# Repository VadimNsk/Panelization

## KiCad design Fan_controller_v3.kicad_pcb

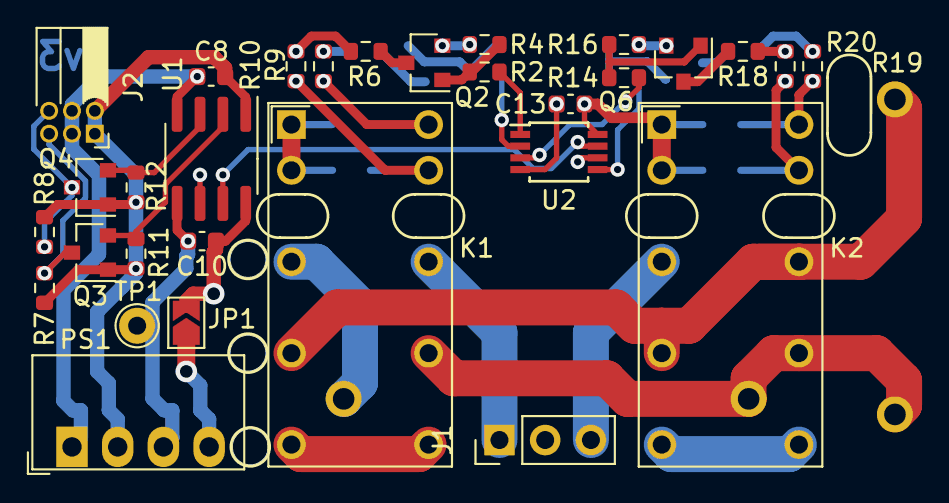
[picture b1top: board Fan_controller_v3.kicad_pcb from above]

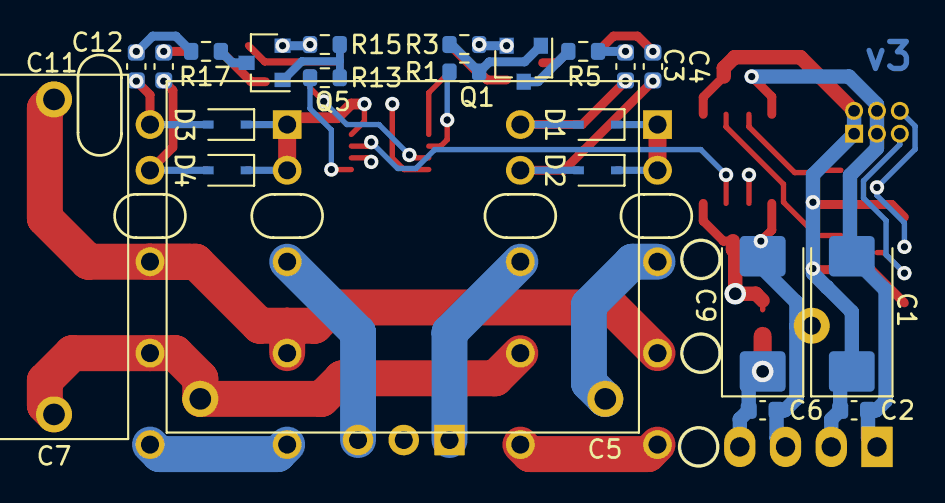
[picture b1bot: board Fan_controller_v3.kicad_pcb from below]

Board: 4 copper layers, 52 parts (22 on the bottom side), 38 nets.

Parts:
C1: 10uF; CP_EIA-7343-43_Kemet-X_Pad2.25x2.55mm_HandSolder
C2, C6, C8, C10, C13: 100nF; C_0603_1608Metric
C3, C4, C11, C12: 10uF; C_0603_1608Metric
C5: 0.47uF; C_K73-17_W26.0mm_H15.0mm_T9.0mm_P22.5mm_d0.8mm_Horiz2
C7: 0.22uF; C_K73-17_W20.0mm_H14.5mm_T8.0mm_P17.5mm_d0.8mm
C9: 100uF; CP_EIA-7343-43_Kemet-X_Pad2.25x2.55mm_HandSolder
D1, D2, D3, D4: 1N4148WS; D_SOD-323
J1: Load2; PinHeader_1x03_P2.54mm
J2: Dig_mod_iface; PinSocket_2x03_P1.27mm_Horizontal
JP1: 5P_en; SolderJumper-2_P1.3mm_Open_TrianglePad1.0x1.5mm
K1, K2: HFD2_005-S-L2-D_Split; HFD2-005-S-L2-D
PS1: B0505S
Q1, Q2, Q5, Q6: 2N5551S; SOT-23
Q3, Q4: BSS138; SOT-23
R1, R2, R13, R14: 1k; R_0603_1608Metric
R3, R4, R15, R16: 20k; R_0603_1608Metric
R5, R6, R17, R18: 47; R_0603_1608Metric
R7, R8: 10G; R_0603_1608Metric
R9, R10, R19, R20: 820; R_0603_1608Metric
R11, R12: 10k; R_0603_1608Metric
TP1: GND; TestPoint_THTPad_D2.0mm_Drill1.0mm
U1: ADuM1251ARZ; SOIC-8_3.9x4.9mm_P1.27mm
U2: PCA9536DP; TSSOP-8_3x3mm_P0.65mm

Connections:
+5P: C1.1, C2.2, C8.2, J2.1, J2.2, PS1.2, Q3.1, Q4.1, R7.2, R8.2, R11.2, R12.2, U1.1
+5VP: C10.2, C13.1, D1.1, D2.1, D3.1, D4.1, JP1.2, K1.1, K1.2, K2.1, K2.2, U1.8, U2.8
/I2C_SCL: U1.6, U2.6
/I2C_SDA: U1.7, U2.7
/K1_rst: R2.2, U2.1
/K1_set: R1.2, U2.2
/K2_rst: R14.2, U2.3
/K2_set: R13.2, U2.5
/scl0: J2.6, Q4.3, R8.1
/sda0: J2.5, Q3.3, R7.1
GND1: C1.2, C2.1, C8.1, J2.3, J2.4, PS1.1, U1.4
GND2: C6.1, C9.2, C10.1, C13.2, PS1.3, Q1.2, Q2.2, Q5.2, Q6.2, R3.2, R4.2, R15.2, R16.2, TP1.1, U1.5, U2.4
unnamed: C3.1, R5.2, R9.1
unnamed: C3.2, D1.2, K1.16, R9.2
unnamed: C4.1, R6.2, R10.1
unnamed: C4.2, D2.2, K1.15, R10.2
unnamed: C5.1, K1.4
unnamed: C5.2, C7.2, K1.11, K2.11
unnamed: C6.2, C9.1, JP1.1, PS1.4
unnamed: C7.1, K1.6, K2.6, K2.13
unnamed: C11.1, R17.2, R19.1
unnamed: C11.2, D3.2, K2.16, R19.2
unnamed: C12.1, R18.2, R20.1
unnamed: C12.2, D4.2, K2.15, R20.2
unnamed: J1.1, K1.13
unnamed: J1.3, K2.4
unnamed: K1.8, K1.9
unnamed: K2.8, K2.9
unnamed: Q1.1, R1.1, R3.1
unnamed: Q1.3, R5.1
unnamed: Q2.1, R2.1, R4.1
unnamed: Q2.3, R6.1
unnamed: Q3.2, R11.1, U1.2
unnamed: Q4.2, R12.1, U1.3
unnamed: Q5.1, R13.1, R15.1
unnamed: Q5.3, R17.1
unnamed: Q6.1, R14.1, R16.1
unnamed: Q6.3, R18.1

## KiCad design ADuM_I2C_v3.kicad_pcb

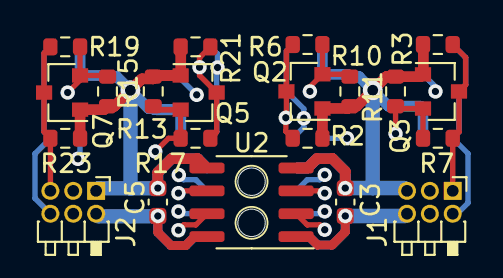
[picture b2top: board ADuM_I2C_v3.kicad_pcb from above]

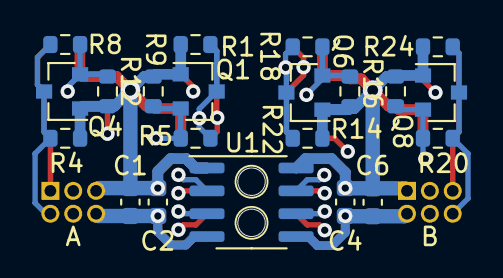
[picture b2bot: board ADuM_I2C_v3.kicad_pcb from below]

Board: 4 copper layers, 42 parts (21 on the bottom side), 20 nets.

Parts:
C1, C6: 1uF; C_0603_1608Metric
C2, C3, C4, C5: 100nF; C_0603_1608Metric
J1: A; PinHeader_2x03_P1.27mm_Horizontal_short
J2: B; PinHeader_2x03_P1.27mm_Horizontal_short
Q1, Q2, Q3, Q4, Q5, Q6, Q7, Q8: BSS138; SOT-23
R1, R2, R3, R4, R21, R22, R23, R24: 2.2M; R_0603_1608Metric
R5, R6, R7, R8, R17, R18, R19, R20: 0; R_0603_1608Metric
R9, R10, R11, R12, R13, R14, R15, R16: 10k; R_0603_1608Metric
U1: ADuM1251ARZ; SOIC-8_3.9x4.9mm_P1.27mm
U2: ADuM1201AR; SOIC-8_3.9x4.9mm_P1.27mm

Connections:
/SCL: J1.4, Q2.3, R2.1, R6.2
/SCLq: J2.4, Q6.3, R18.1, R22.1
/SDA: J1.3, Q1.3, R1.1, R5.2
/SDAq: J2.3, Q5.3, R17.1, R21.1
/ina: J1.1, Q3.3, R3.1, R7.2
/inb: J2.6, Q8.3, R20.1, R24.1
/outa: J2.5, Q7.3, R19.1, R23.1
/outb: J1.2, Q4.3, R4.1, R8.2
GND: C1.1, C2.1, C3.1, J1.6, U1.4, U2.1
GND2: C4.1, C5.1, C6.1, J2.2, U1.5, U2.8
unnamed: Q1.2, R5.1, R9.2, U1.2
unnamed: Q2.2, R6.1, R10.2, U1.3
unnamed: Q3.2, R7.1, R11.2, U2.3
unnamed: Q4.2, R8.1, R12.2, U2.2
unnamed: Q5.2, R13.2, R17.2, U1.7
unnamed: Q6.2, R14.2, R18.2, U1.6
unnamed: Q7.2, R15.2, R19.2, U2.6
unnamed: Q8.2, R16.2, R20.2, U2.7
VCC: C1.2, C2.2, C3.2, J1.5, Q1.1, Q2.1, Q3.1, Q4.1, R1.2, R2.2, R3.2, R4.2, R9.1, R10.1, R11.1, R12.1, U1.1, U2.4
VCCQ: C4.2, C5.2, C6.2, J2.1, Q5.1, Q6.1, Q7.1, Q8.1, R13.1, R14.1, R15.1, R16.1, R21.2, R22.2, R23.2, R24.2, U1.8, U2.5

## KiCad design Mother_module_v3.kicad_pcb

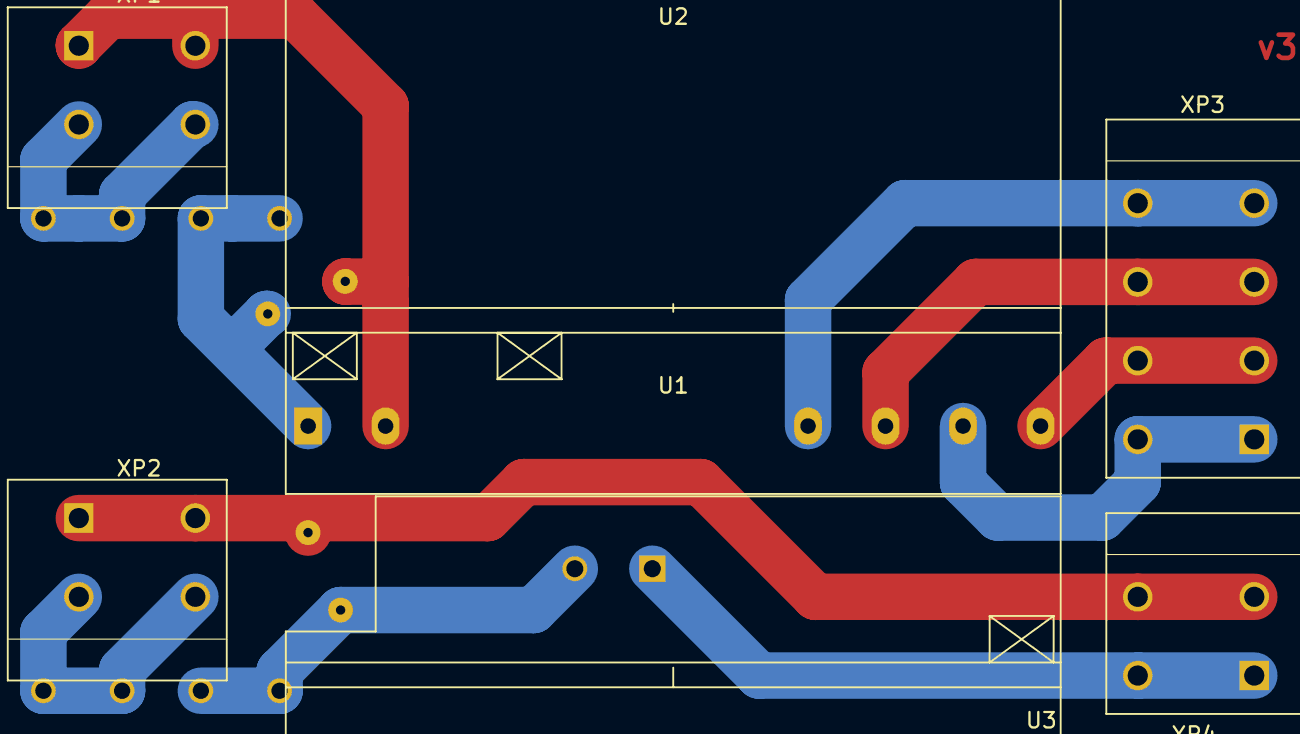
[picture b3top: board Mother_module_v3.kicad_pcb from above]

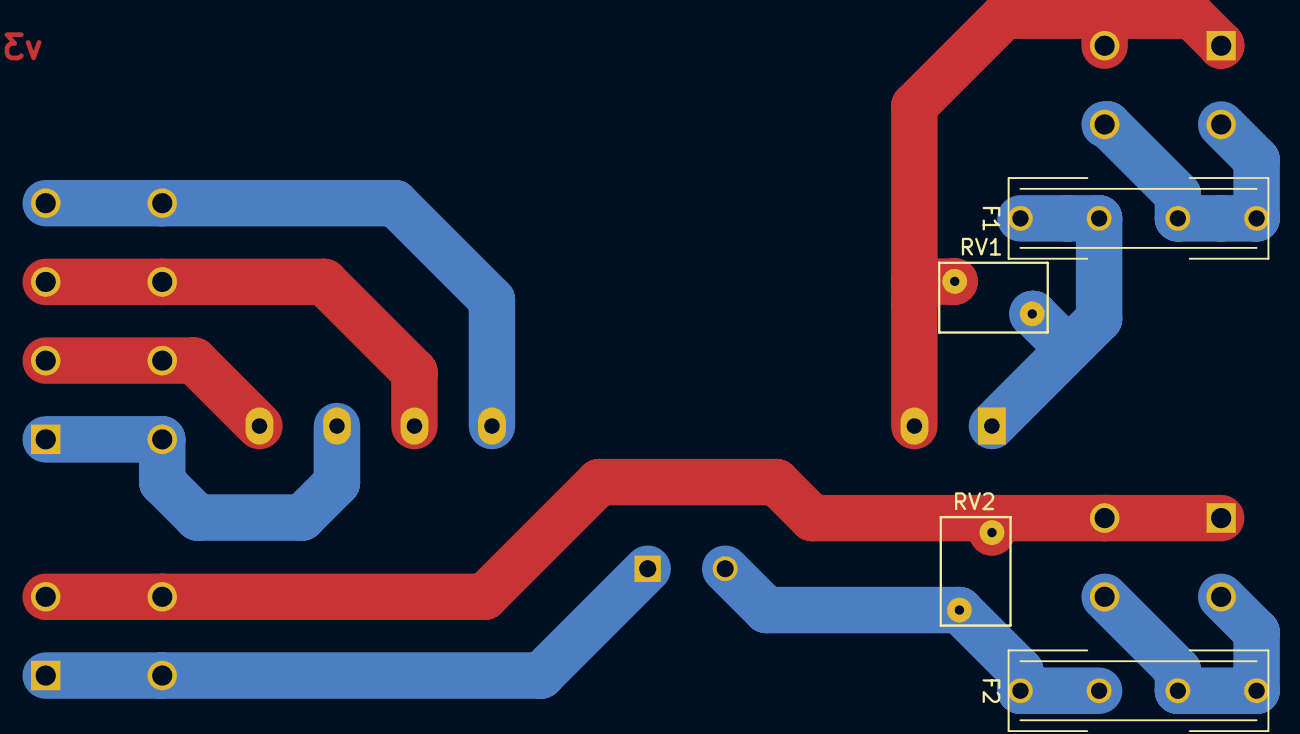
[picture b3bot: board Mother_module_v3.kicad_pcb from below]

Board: 2 copper layers, 11 parts (4 on the bottom side), 11 nets.

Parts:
F1, F2: 0.5A; FC-05C-E_4x15
RV1, RV2: 470V; RV_Disc_D7mm_W4.5mm_P5mm
U1: Virtual_Digital_module_v3
U2: Power_manager_v3-Modules; Power_manager_v3
U3: Fan_control_module_v3; Fan_controller_v3
XP1, XP2: ACin; XY122R-5.08-02P-14
XP3: LoadX; XY122R-5.08-04P-14
XP4: LoadX; XY122R-5.08-02P-14

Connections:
unnamed: F1.1, RV1.1, U2.1
unnamed: F1.2, XP1.2
unnamed: F2.1, RV2.1, U3.2
unnamed: F2.2, XP2.2
unnamed: RV1.2, U2.2, XP1.1
unnamed: RV2.2, XP2.1, XP4.2
unnamed: U2.3, XP3.4
unnamed: U2.4, XP3.3
unnamed: U2.5, XP3.1
unnamed: U2.6, XP3.2
unnamed: U3.1, XP4.1

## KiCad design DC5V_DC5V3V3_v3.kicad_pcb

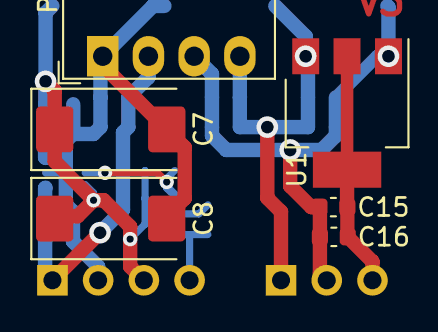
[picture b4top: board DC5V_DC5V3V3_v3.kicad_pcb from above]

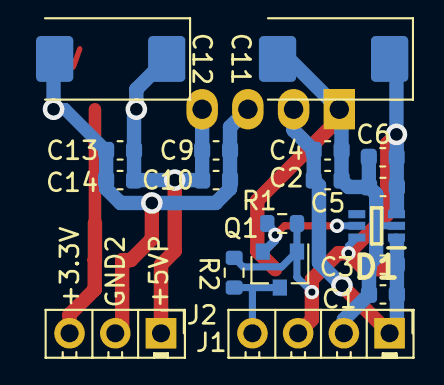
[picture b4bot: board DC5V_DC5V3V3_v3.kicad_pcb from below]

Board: 2 copper layers, 24 parts (18 on the bottom side), 8 nets.

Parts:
C1, C2, C6, C10, C13, C16: 10uF; C_0603_1608Metric
C3, C4, C5, C9, C14, C15: 100nF; C_0603_1608Metric
C7, C8: 470uF; CP_EIA-7343-31_Kemet-D
C11, C12: 470uF; CP_EIA-7343-15_Kemet-W
D1: LM66100DCKR; SOP65P210X110-6N
J1: Vout1; PinHeader_1x04_P2.54mm_Horizontal_short
J2: Vout2; PinHeader_1x03_P2.54mm_Horizontal_short
PS1: B0505S
Q1: BSS138; SOT-23
R1: 10k; R_0603_1608Metric
R2: 2.2M; R_0603_1608Metric
U1: LM1117-3.3; SOT-223-3_TabPin2

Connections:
+3.3VP: C15.2, C16.2, J2.3, U1.2
+5P: C5.2, C6.2, C7.1, C8.1, C11.1, D1.3, D1.6, J1.3, Q1.1, R1.1, R2.2
+5V: C1.2, C2.2, C3.2, C4.2, D1.1, J1.1, PS1.2
+5VP: C9.2, C10.2, C12.1, C13.2, C14.2, J2.1, PS1.4, U1.3
/+5V_state: J1.4, Q1.3, R2.1
GND1: C1.1, C2.1, C3.1, C4.1, C5.1, C6.1, C7.2, C8.2, C11.2, D1.2, J1.2, PS1.1
GND2: C9.1, C10.1, C12.2, C13.1, C14.1, C15.1, C16.1, J2.2, PS1.3, U1.1
unnamed: D1.5, Q1.2, R1.2

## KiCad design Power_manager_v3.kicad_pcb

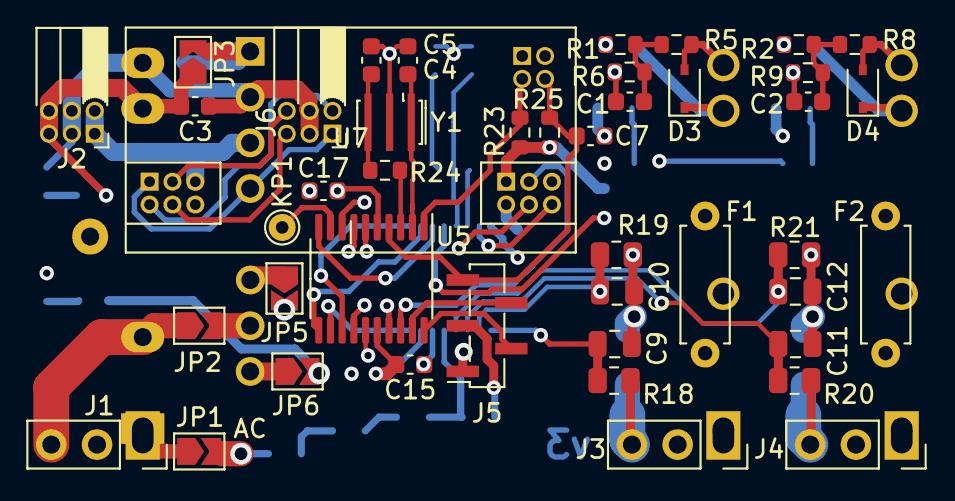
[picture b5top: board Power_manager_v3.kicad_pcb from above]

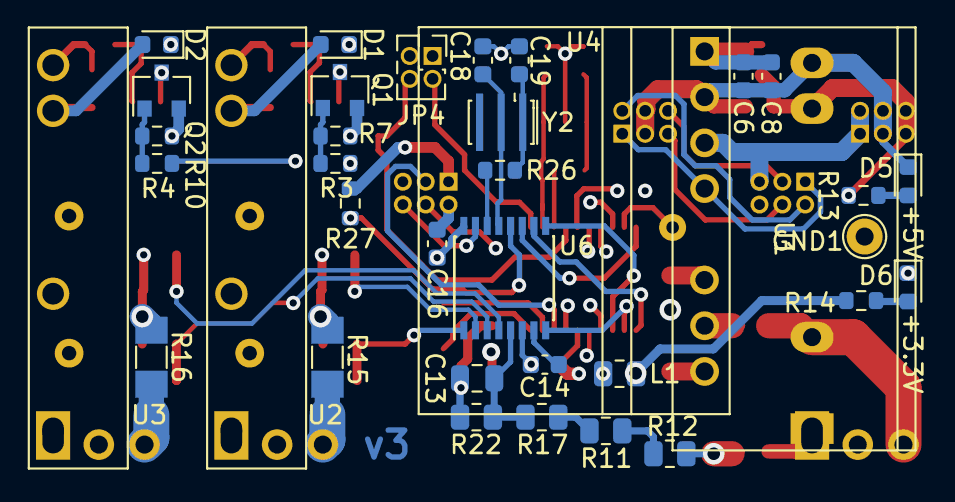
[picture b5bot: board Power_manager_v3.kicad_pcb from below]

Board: 4 copper layers, 80 parts (36 on the bottom side), 65 nets.

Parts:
C1, C2, C3, C7, C8, C14, C15, C16, C17: 100nF; C_0603_1608Metric
C4, C5: 10pF; C_0603_1608Metric
C6: 10uF; C_0603_1608Metric
C9, C10, C11, C12: 330nF; C_0805_2012Metric
C13: 33nF; C_0805_2012Metric
C18, C19: 22pF; C_0603_1608Metric
D1, D2: LED; LED_0603_1608Metric
D3, D4: 1N4148WS; D_SOD-323
D5: +5V; LED_0603_1608Metric
D6: +3.3VP; LED_0603_1608Metric
F1, F2: 0.5A; R_Axial_DIN0207_L6.3mm_D2.5mm_P7.62mm_Horizontal
GND1: TestPoint_Small; TestPoint_THTPad_D2.0mm_Drill1.0mm
J1: L_input; PinHeader_1x03_P2.54mm_Vertical_for_DG301-5.0-02P
J2: Pow_mng_pow; PinSocket_2x03_P1.27mm_Horizontal
J3: Load1; PinHeader_1x03_P2.54mm_Vertical_for_DG301-5.0-02P
J4: Load2; PinHeader_1x03_P2.54mm_Vertical_for_DG301-5.0-02P
J5: SWD (PLS5); PinSocket_1x05_P1.27mm_Vertical_SMD_Pin1Right
J6: Dig_mod_iface; PinSocket_2x03_P1.27mm_Horizontal
JP1: AC_en; SolderJumper-2_P1.3mm_Open_TrianglePad1.0x1.5mm
JP2: N_en; SolderJumper-2_P1.3mm_Open_TrianglePad1.0x1.5mm
JP3: 5V_en; SolderJumper-2_P1.3mm_Open_TrianglePad1.0x1.5mm
JP4: Jumper_2x2_Open; PinHeader_2x02_P1.27mm_Vertical
JP5: 5VP_en; SolderJumper-2_P1.3mm_Open_TrianglePad1.0x1.5mm
JP6: 3.3VP_en; SolderJumper-2_P1.3mm_Open_TrianglePad1.0x1.5mm
KP1: TestPoint_Small; TestPoint_THTPad_D1.5mm_Drill0.7mm
L1: 22u*; R_0805_2012Metric
Q1, Q2: 2N5551S; SOT-23
R1, R2: 360; R_0603_1608Metric
R3, R4: 1k; R_0603_1608Metric
R5, R8: 220; R_0603_1608Metric
R6, R9: 470; R_0603_1608Metric
R7, R10: 20k; R_0603_1608Metric
R11, R12, R17: 332k; R_0805_2012Metric
R13, R14, R23, R25, R27: 10k; R_0603_1608Metric
R15, R16: 0.001; R_MiniMELF_MMA-0204
R18, R19, R20, R21: 100; R_0805_2012Metric
R22: 1k; R_0805_2012Metric
R24, R26: 50; R_0603_1608Metric
U1: DC12003
U2, U3: G3MB-202PL
U4: DC5V_DC5V3V3_v3
U5: STM32F030F4Px; TSSOP-20_4.4x6.5mm_P0.65mm
U6: HLW8112; SSOP-16_4.4x5.2mm_P0.65mm
U7: ADuM_I2C_v3; ADuM_I2C_Horizontal
Y1: CSTCE8M; Resonator_SMD_muRata_CSTxExxV-3Pin_3.0x1.1mm_HandSoldering
Y2: ABLS-3.579545MHZ-D-3-Y-T; Resonator_SMD_muRata_CSTxExxV-3Pin_3.0x1.1mm_HandSoldering

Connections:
+3.3VP: C15.1, C16.2, J5.1, JP6.2, L1.1, R14.2, R23.2, R25.1, R27.1, U5.16, U6.16, U7.B1
+5P: J2.1, J2.2, U4.3, U7.A5
+5V: C3.2, J2.5, J2.6, JP3.1, R13.2, U1.3
+5VP: D1.2, D2.2, D3.1, D4.1, JP5.2, U2.3, U3.3
/+5V_state: J6.1, U4.4, U7.A1
/+5V_valid: U5.14, U7.B5
/I2C_Int: J6.2, U7.A2
/I2C_SCL: U5.17, U7.B4
/I2C_SDA: U5.18, U7.B3
/Int: U5.6, U6.15, U7.B6
/L1_o1_nEn: R3.2, U5.7
/L1_o2_nEn: R4.2, U5.8
/Load1N: J3.3, R15.1, R18.1
/Load2N: J4.3, R16.1, R20.1
/SPI_MISO: U5.12, U6.8
/SPI_MOSI: U5.13, U6.9
/SPI_SCLK: U5.11, U6.10
/SPI_SSEL: U5.10, U6.11
/SWCLK: J5.2, U5.20
/SWDIO: J5.4, U5.19
/nRst: C7.1, J5.5, JP4.4, R25.2, U5.4
/scl0: J6.5, U7.A4
/sda0: J6.6, U7.A3
AC: F1.1, F2.1, JP1.2, R12.2
GND1: C3.1, C6.1, C8.1, D5.1, GND1.1, J2.3, J2.4, J6.3, J6.4, U1.4, U4.2, U7.A6
GNDPWR: C4.2, C5.2, C7.2, C9.1, C10.2, C11.1, C12.2, C13.1, C14.1, C15.2, C16.1, C17.1, C18.1, C19.1, D6.1, J5.3, JP2.2, JP4.1, JP4.3, Q1.2, Q2.2, R7.2, R10.2, R15.2, R16.2, R19.1, R21.1, R22.2, U4.6, U5.15, U6.6, U7.B2, Y1.2
unnamed: C1.1, Q1.3, R6.2
unnamed: C1.2, R1.1, R5.1, R6.1
unnamed: C2.1, Q2.3, R9.2
unnamed: C2.2, R2.1, R8.1, R9.1
unnamed: C4.1, U5.2, Y1.1
unnamed: C5.1, R24.1, Y1.3
unnamed: C6.2, C8.2, JP3.2, U4.1
unnamed: C9.2, R18.2, U6.1
unnamed: C10.1, R19.2, U6.2
unnamed: C11.2, R20.2, U6.3
unnamed: C12.1, R21.2, U6.4
unnamed: C13.2, R17.1, R22.1, U6.5
unnamed: C14.2, U6.7
unnamed: C17.2, L1.2, U5.5
unnamed: C18.2, U6.13, Y2.2
unnamed: C19.2, R26.2, Y2.1
unnamed: D1.1, R1.2
unnamed: D2.1, R2.2
unnamed: D3.2, R5.2, U2.4
unnamed: D4.2, R8.2, U3.4
unnamed: D5.2, R13.1
unnamed: D6.2, R14.1
unnamed: F1.2, U2.2
unnamed: F2.2, U3.2
unnamed: J1.1, JP1.1, U1.1
unnamed: J1.3, JP2.1, U1.2
unnamed: J3.1, U2.1
unnamed: J4.1, U3.1
unnamed: JP4.2, R23.1, U5.1
unnamed: JP5.1, U4.5
unnamed: JP6.1, U4.7
unnamed: KP1.1, U5.9
unnamed: Q1.1, R3.1, R7.1
unnamed: Q2.1, R4.1, R10.1
unnamed: R11.1, R17.2
unnamed: R11.2, R12.1
unnamed: R24.2, U5.3
unnamed: R26.1, U6.14
unnamed: R27.2, U6.12

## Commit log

2022-01-18 Добавлены файлы панелизации. Добавлен BOM-файл в HTML-формате, гербера и файлы сверловки.
2022-01-18 Переделана панелизация платы ADuM_I2C_v3
2022-01-18 Сформирован перечень элементов, 3D-модель, исправлены ошибки, реализована панелизация платы.
2022-01-19 Созданы две панели: односторонняя и двухсторонняя, объединяющие все платы, кроме цифрового модуля. Добавлен окантовка по контуру платы с двух сторон и текст: "JLCJLCJLCJLC"
2022-02-17 Последние изменения в BOM
